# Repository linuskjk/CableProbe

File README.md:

# CableProbe

A custom ESP32-based tool to analyze and verify USB-C cables.

## TO THE REVIEWER PLEASE READ THE MESSAGE AT THE BOTTOM ;)
## Features

### Analysis
- Basic connectivity check
- Problem detection
- Power throughput & quality
- Fast Charging / Power Delivery support
- General-purpose suitability testing

## Hardware

- ESP32 on a custom PCB
- 2x USB-C modules linked to GPIOs
- 128x64 SSD1306 OLED display
- Basic resistor setup for pin pulling

## Why?

Ever bought a pile of cheap USB-C cables from AliExpress only to find out they are bad? Or struggled to figure out which cable actually supports fast charging?

CableProbe was made to quickly sort through the cable drawer. It identifies the quality and features of almost any USB-C cable without needing a PC or complicated setup.

## Usage

Simply plug both ends of your cable into the USB-C modules and follow the instructions on the screen.

The ESP32 will run through the pins and display the results on the screen. It immediately tells you whether the cable is suitable for:
- charging only,
- fast charging,
- or high-speed applications.

## Images

### Case

### PCB

### ROUTING

### SCHEMATIC

### CASE
## IMPORTANT: THIS IS NOT THE NEWEST VERSION OF THE CASE BUT IT USES THE EXACT SAME FRICTION FIT SO IT ALSO WORKS ON THE NEW VERSION.

https://github.com/user-attachments/assets/e5118ca8-60bc-48c1-94f0-9f646d53b27a

### PROOF THAT MY FRICTION FIT WORKS

https://github.com/user-attachments/assets/f6ddad3f-a20b-4f4a-b254-9df56e5059d4

# Build Your Own

## PCB and Parts

| Reference         | Qty | Value         | Description                                      | Price EUR | Pack Info | Link                                                        |
| ----------------- | --: | ------------- | ------------------------------------------------ | --------: | --------- | ----------------------------------------------------------- |
| Brd1              |   1 | 128x64 OLED   | SSD1306                                          |      2.89 | 1 pc      | [Buy](https://de.aliexpress.com/item/1005006514489341.html) |
| R1 R2 R3 R4 R5 R6 |   6 | 1k Ohm        | R_Axial_DIN0207_L6.3mm_D2.5mm_P7.62mm_Horizontal |      3.30 | 20 pcs    | [Buy](https://amzn.eu/d/0aSOhZVj)                           |
| U1 U2             |   2 | USB-C Module  | USB-C connector module to connect the cable to   |      1.61 | 5 pcs     | [Buy](https://de.aliexpress.com/item/1005007314733520.html) |
| U3                |   1 | ESP32-DevKitC | ESP32 development board                          |      2.99 | 1 pc      | [Buy](https://de.aliexpress.com/item/1005006140555903.html) |
| Battery | 1 | 654060 Li-Po 200mAh | Lithium polymer battery | 9.90 | 1 pc | [Buy](https://de.aliexpress.com/item/1005005970679252.html) |
| Charger Module | 1 | TP4057 | USB-C charging module | 3.83 | 1 pc | [Buy](https://de.aliexpress.com/item/1005010764961491.html) |

The PCB is a simple custom design made to hold the ESP32, USB-C modules, and OLED display in a compact enclosure.

## Soldering 

Recommended order:
1. Resistors
2. ESP32
3. USB-C modules
4. OLED display

No special equipment needed.

## Case

3D print the provided STL files.

Both PLA and PETG work perfectly fine. I recommend using PLA. 
I have already printed and tested the case. The friction fit works perfectly, and the battery mount fits exactly as intended. The PCB and firmware have also been tested and are working correctly.

## Programming 

**Install the following libraries** (you can find them under firmware/libraries or the library manager:
- *Adafruit_GFX.h*
- *Adafruit_SSD1306.h*

**Flashing** is straightforward:
1. Open 'main.ino' from the 'firmware' folder in your preferred IDE.
2. Select the correct ESP32 board (ESP32 DevKit).
3. Hit upload

## Assembly 

1. Drop the PCB into the bottom half of the case
2. Connect the battery to the charger module (B+/- to the battery terminals and the module output to V+/GND). The charger module is intentionally not mounted on the PCB to save space and allow more flexible battery placement. Simply press the module into the slot at the bottom of the case. It fits securely and withstands considerable force.
3. Align the USB-C ports with the openings
4. Fit the OLED display into place
5. Close the enclosure

To the reviewer: I cant resubmit this anymore so if you reject it I have some serious problems. I already booked my flights and bought a laptop just for the event. I am going homeless if I cant go. But IF there is a problem with my project, can you just not reject it but tell me what to do and after it is done you can approve it. PLEASE. and also if you are wondering about the 3D models of the USB-C modules on the PCB, I unfortunately couldn't find any suitable 3D models for them and was advised to leave them as they are.

Everything is designed to fit snugly without additional hardware.

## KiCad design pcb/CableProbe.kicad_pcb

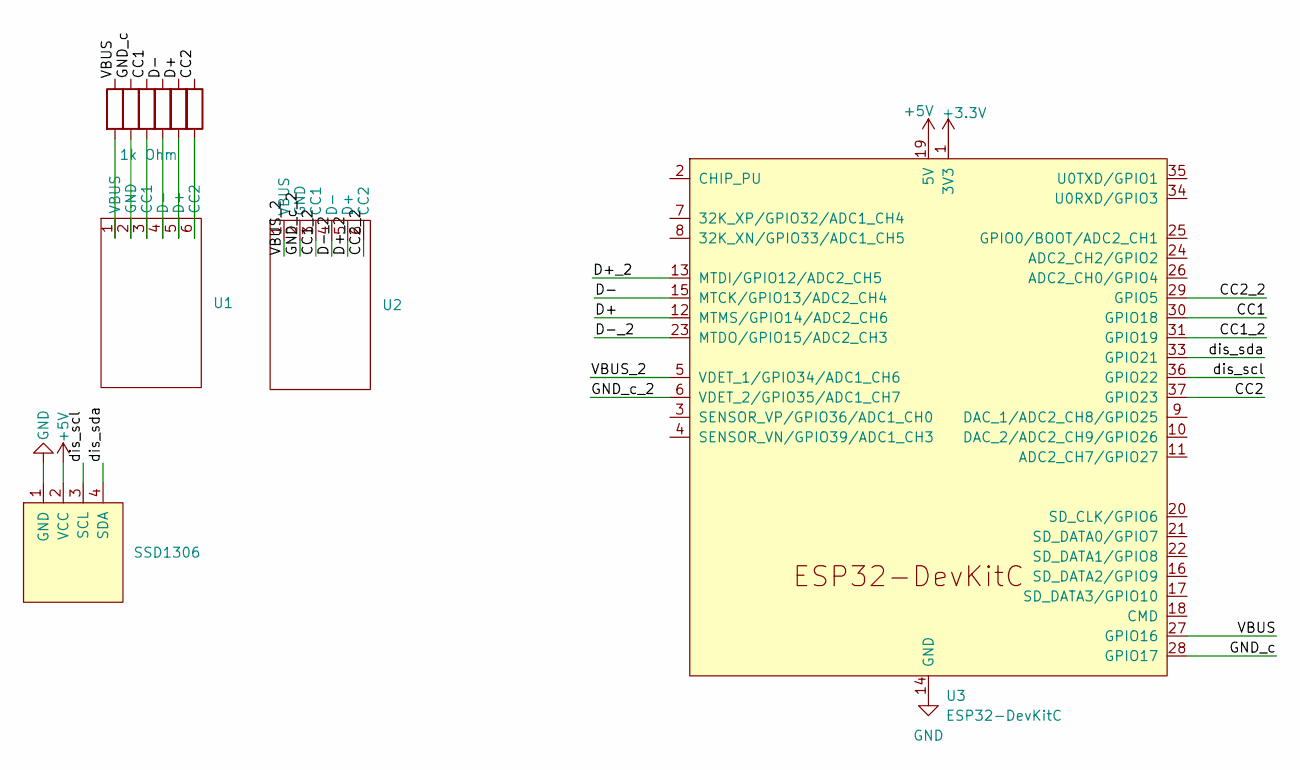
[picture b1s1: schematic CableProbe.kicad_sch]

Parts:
Brd1: SSD1306; 128x64OLED
R1, R2, R3, R4, R5, R6: 1k Ohm; R_Axial_DIN0207_L6.3mm_D2.5mm_P7.62mm_Horizontal
U1, U2: usbc_bb
U3: ESP32-DevKitC

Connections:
+3.3V: U3.1 (3V3)
+5V: Brd1.2 (VCC), U3.19 (5V)
/CC1: R3.1, U3.30 (GPIO18)
/CC1_2: U2.3 (CC1), U3.31 (GPIO19)
/CC2: R6.1, U3.37 (GPIO23)
/CC2_2: U2.6 (CC2), U3.29 (GPIO5)
/D+: R5.1, U3.12 (MTMS/GPIO14/ADC2_CH6)
/D+_2: U2.5 (D+), U3.13 (MTDI/GPIO12/ADC2_CH5)
/D-: R4.1, U3.15 (MTCK/GPIO13/ADC2_CH4)
/D-_2: U2.4 (D-), U3.23 (MTDO/GPIO15/ADC2_CH3)
/GND_c: R2.1, U3.28 (GPIO17)
/GND_c_2: U2.2 (GND), U3.6 (VDET_2/GPIO35/ADC1_CH7)
/VBUS: R1.1, U3.27 (GPIO16)
/VBUS_2: U2.1 (VBUS), U3.5 (VDET_1/GPIO34/ADC1_CH6)
/dis_scl: Brd1.3 (SCL), U3.36 (GPIO22)
/dis_sda: Brd1.4 (SDA), U3.33 (GPIO21)
GND: Brd1.1 (GND), U3.14 (GND), U3.32 (GND), U3.38 (GND)
unnamed: R3.2, U1.3 (CC1)
unnamed: R6.2, U1.6 (CC2)
unnamed: R5.2, U1.5 (D+)
unnamed: R4.2, U1.4 (D-)
unnamed: R2.2, U1.2 (GND)
unnamed: R1.2, U1.1 (VBUS)

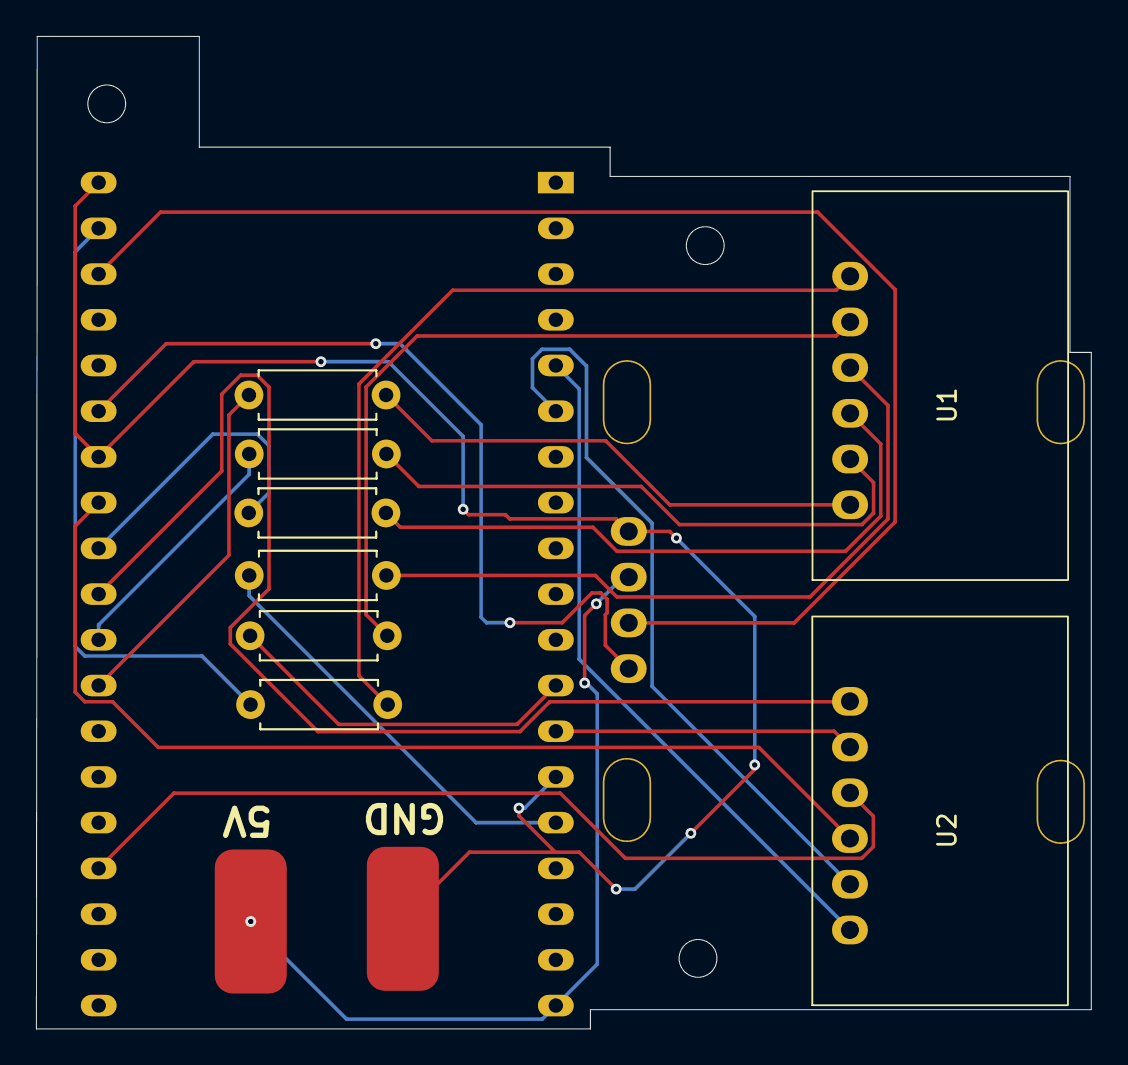
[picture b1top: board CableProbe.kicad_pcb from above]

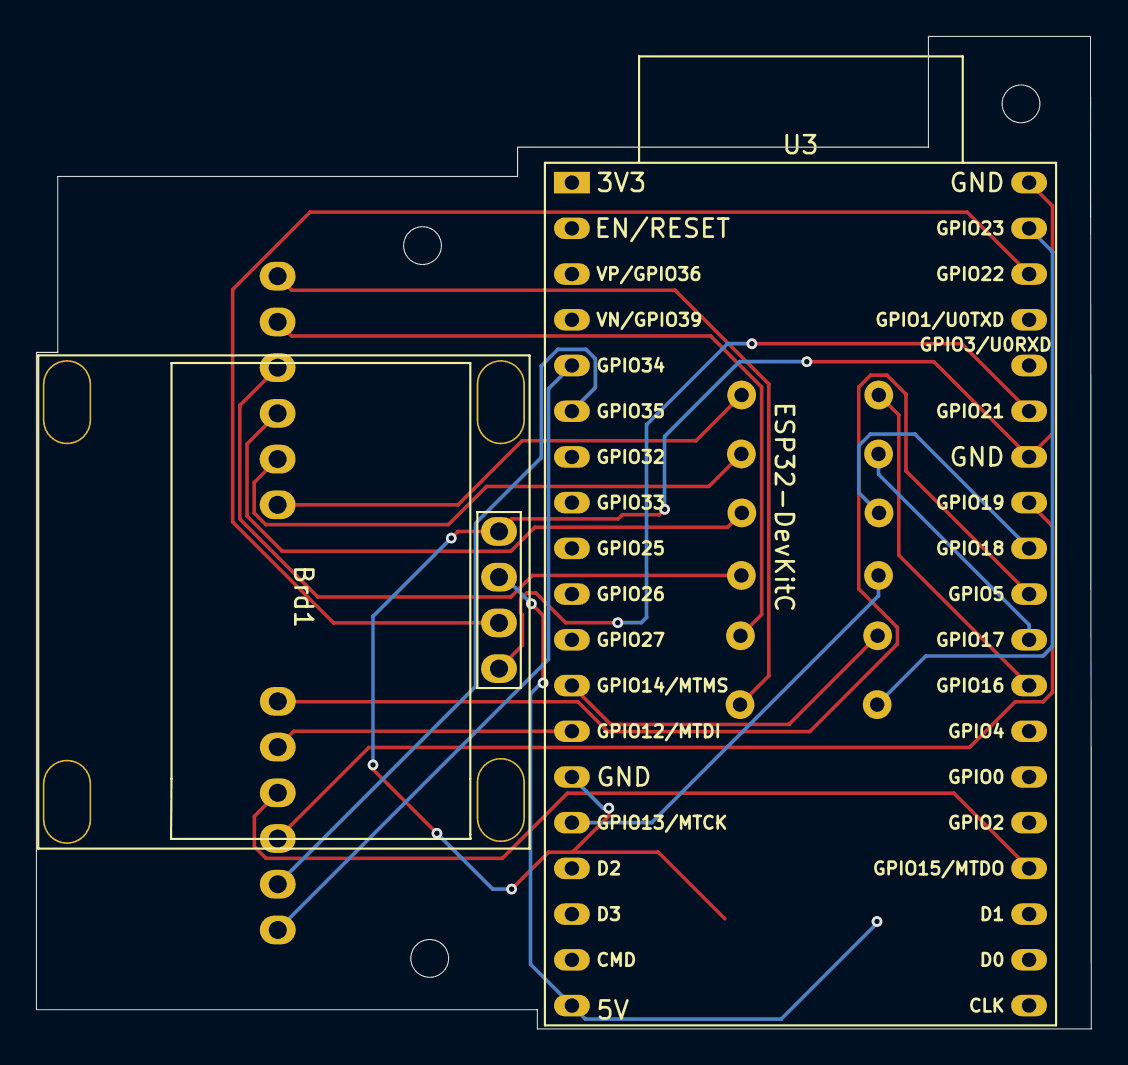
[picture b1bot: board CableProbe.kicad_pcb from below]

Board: 2 copper layers, 58.6 x 55.1 mm, 13 parts (2 on the bottom side), 22 nets.

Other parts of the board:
M1, M2, M3: MountingHole_2.1mm

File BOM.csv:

Reference,Qty,Value,Description,Price EUR,Pack Info,Link
Brd1,1,128x64OLED,SSD1306,2.89,1 pcs,https://de.aliexpress.com/item/1005006514489341.html
"R1, R2, R3, R4, R5, R6",6,1k Ohm,R_Axial_DIN0207_L6.3mm_D2.5mm_P7.62mm_Horizontal,3.30,20 pcs,https://amzn.eu/d/0aSOhZVj
"U1, U2",2,usbc_module,usb-c connector module to connect the cable to,1.61,5,https://de.aliexpress.com/item/1005007314733520.html
U3,1,ESP32-DevKitC,ESP32 development board,2.99,1 pc,https://de.aliexpress.com/item/1005006140555903.html
TOTAL,,,Total price,10.79 / 7.51,,

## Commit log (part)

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2026-06-15 Fixed pcb, zine and case
2026-06-15 Restore missing files
2026-06-15 Rename bom.csv to BOM.csv
